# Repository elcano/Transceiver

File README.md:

# Transceiver
Hardware and software to support Transmit/Receive boards

The Elcano Project is an autonomous vehicle control system that runs on a stack of microprocessors, with no operating system and 
no machine learning.
Files that span more than one processor are kept in Elcano/General. The other repositories are:
Elcano/LowLevel – Drive by wire
Elcano/HighLevel – Localization, Route Finding and Pilot
Elcano/Sonar – Detects obstacles from ultrasonic sensors
Elcano/Sweep – Scanse Sweep Lidar for Obstacle Detection
Elcano/QDED – Quadrature Edge Detectors for machine vision
Elcano/Transceiver – Transmit and receive boards for remote control option

The primary autonomous vehicle control comes from HighLevel. Alternatively, the vehicle can be controlled manually, which is the function 
of the Tranceiver board. Depending on what is soldered into the board and which software is used, there are several configurations of the 
transceiver:
 
Transmitter board with joysticks and switches sending via radio.
Receiver board receiving from radio and putting information on CAN bus.
Transmitter via Bluetooth.
Receiver via Bluetooth.
Receiver from a hobbyist RC controller
User interface with joysticks and switches, putting information on CAN bus.

### Required libraries:

#### *Seeed-Studio/CAN-BUS-Shield*
Download as zip from https://github.com/Seeed-Studio/Seeed_Arduino_CAN. 
In Arduino IDE, go to Sketch -> Include Library -> Add .ZIP Library and select the .zip folder.

#### *elcano/Elcano_C2_LowLevel/Can_Protocol.h*
Download “Can_Protocol.h” from https://github.com/elcano/elcano/tree/master/Elcano_C2_LowLevel. 
Create a folder in the location where the Arduino IDE contains it’s libraries on your computer and add this file to the newly created folder.

#### *http://www.airspayce.com/mikem/arduino/RadioHead/classRH__RF69.html*
Download as zip from http://www.airspayce.com/mikem/arduino/RadioHead/index.html. 
In Arduino IDE, go to Sketch -> Include Library -> Add .ZIP Library and select the .zip folder.

#### *elcano/libraries/Settings/SettingsTemplate.h*
Download “SettingsTemplate.h” from https://github.com/elcano/elcano/tree/master/Elcano_C2_LowLevel. 
Create a folder in the location where the Arduino IDE contains it’s libraries on your computer and add this file to the newly created folder.

#### *scanse/sweep-arduino/tree/master/Sweep*
Download as zip from https://github.com/scanse/sweep-arduino. 
Note: need to unzip zip folder and then compress to zip only the sweep folder.
In Arduino IDE, go to Sketch -> Include Library -> Add .ZIP Library and select the .zip folder.

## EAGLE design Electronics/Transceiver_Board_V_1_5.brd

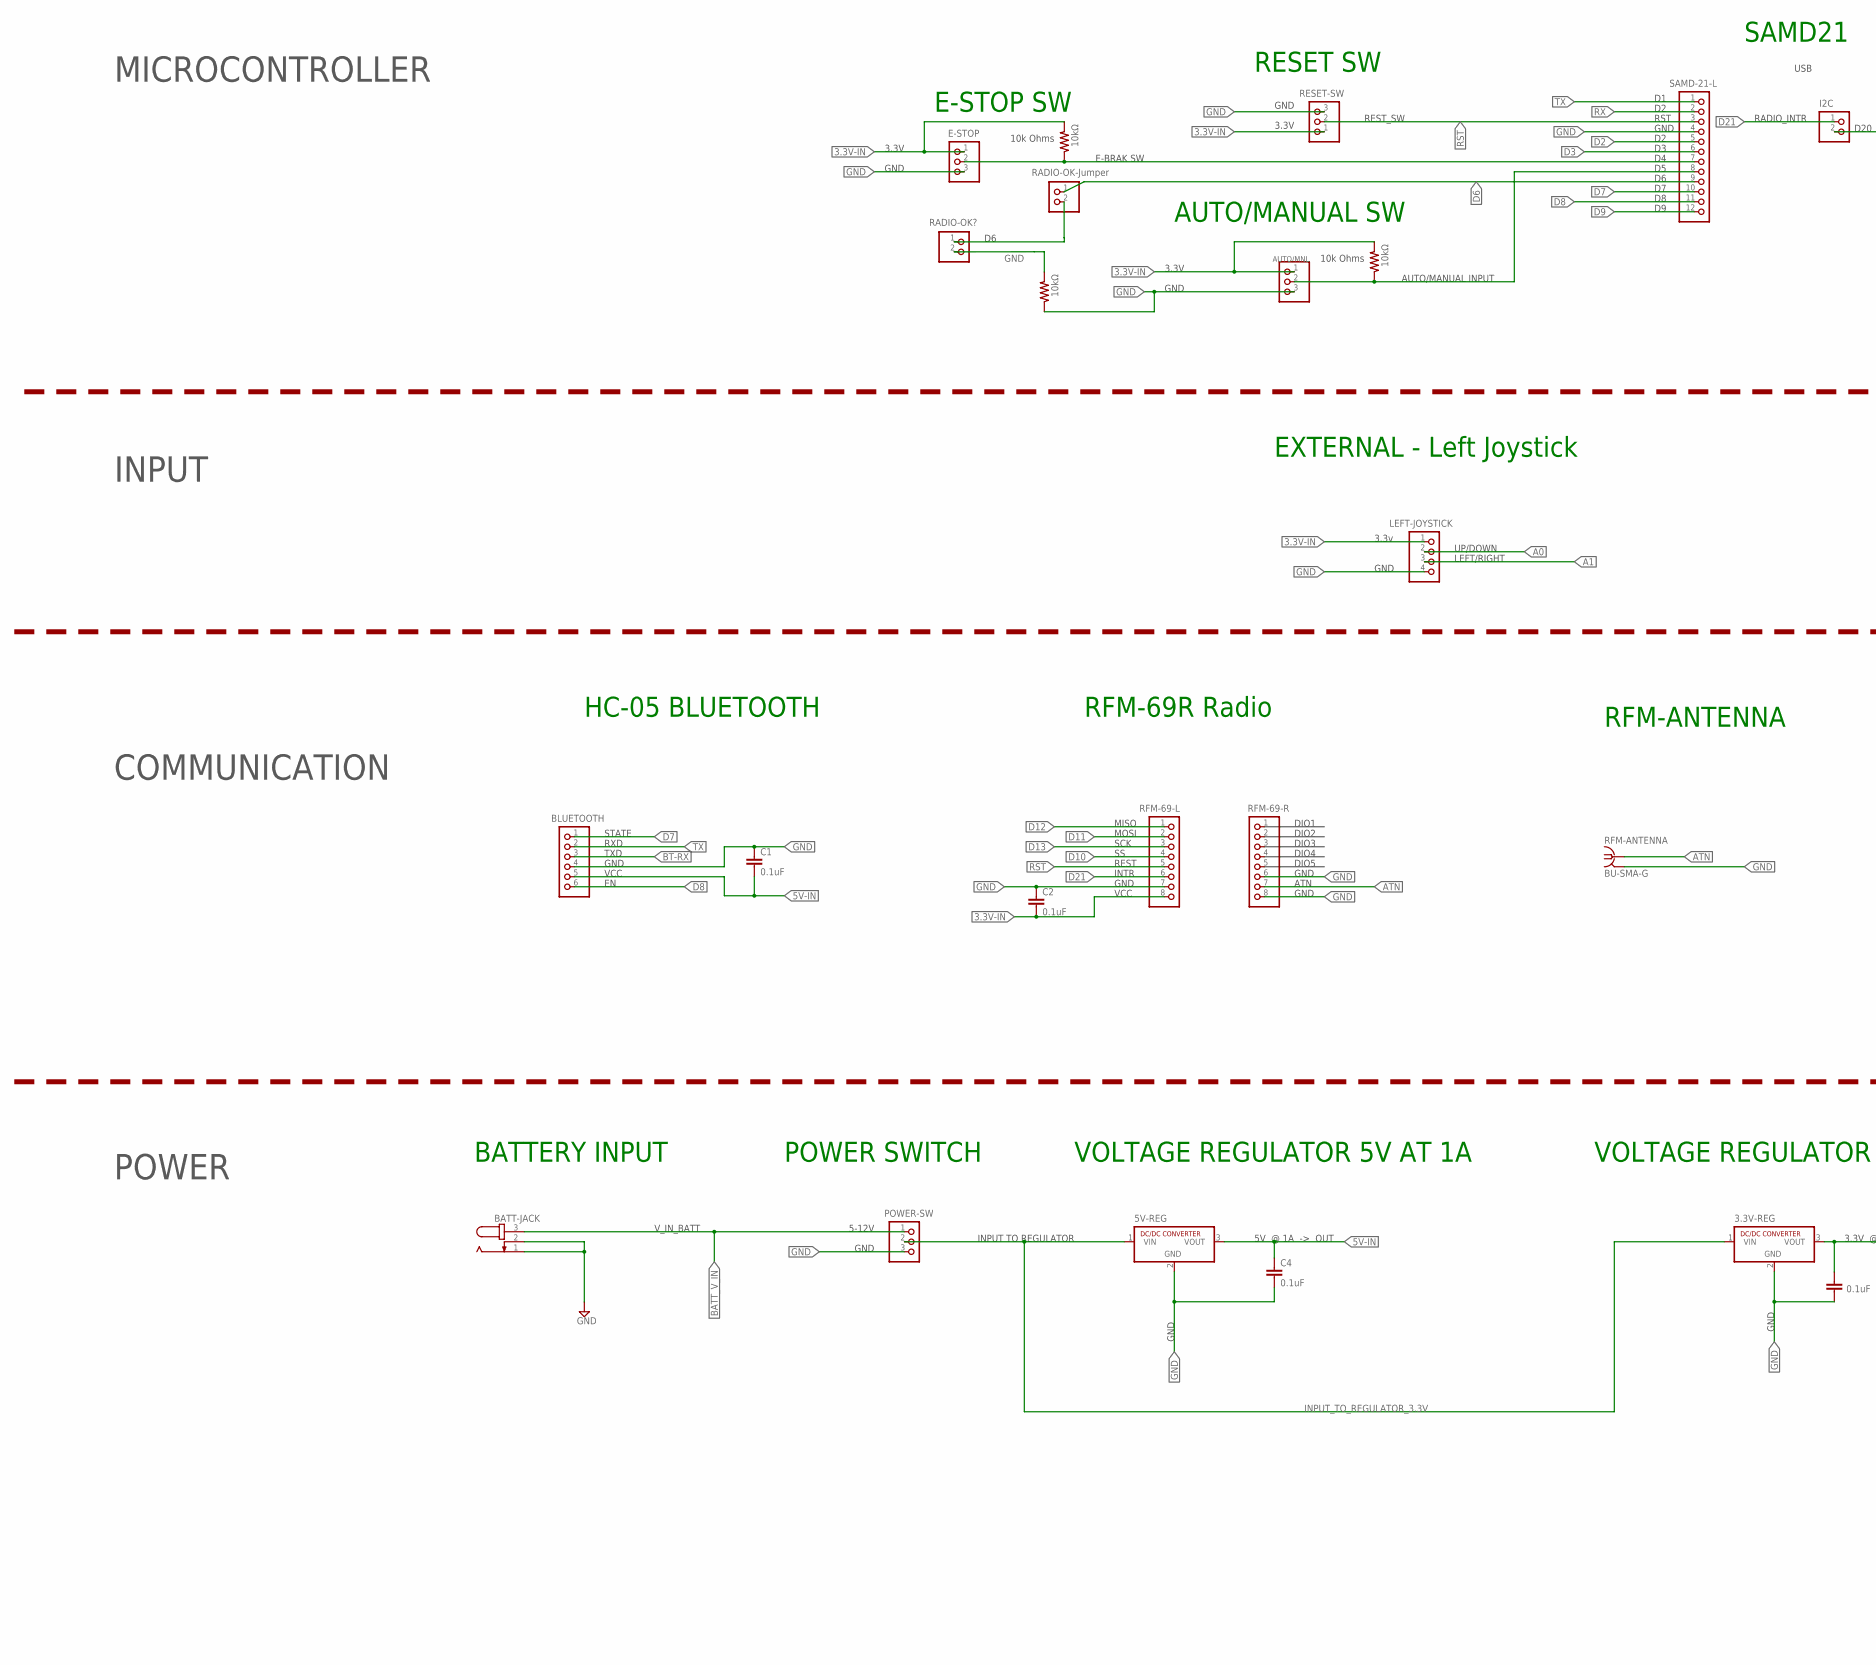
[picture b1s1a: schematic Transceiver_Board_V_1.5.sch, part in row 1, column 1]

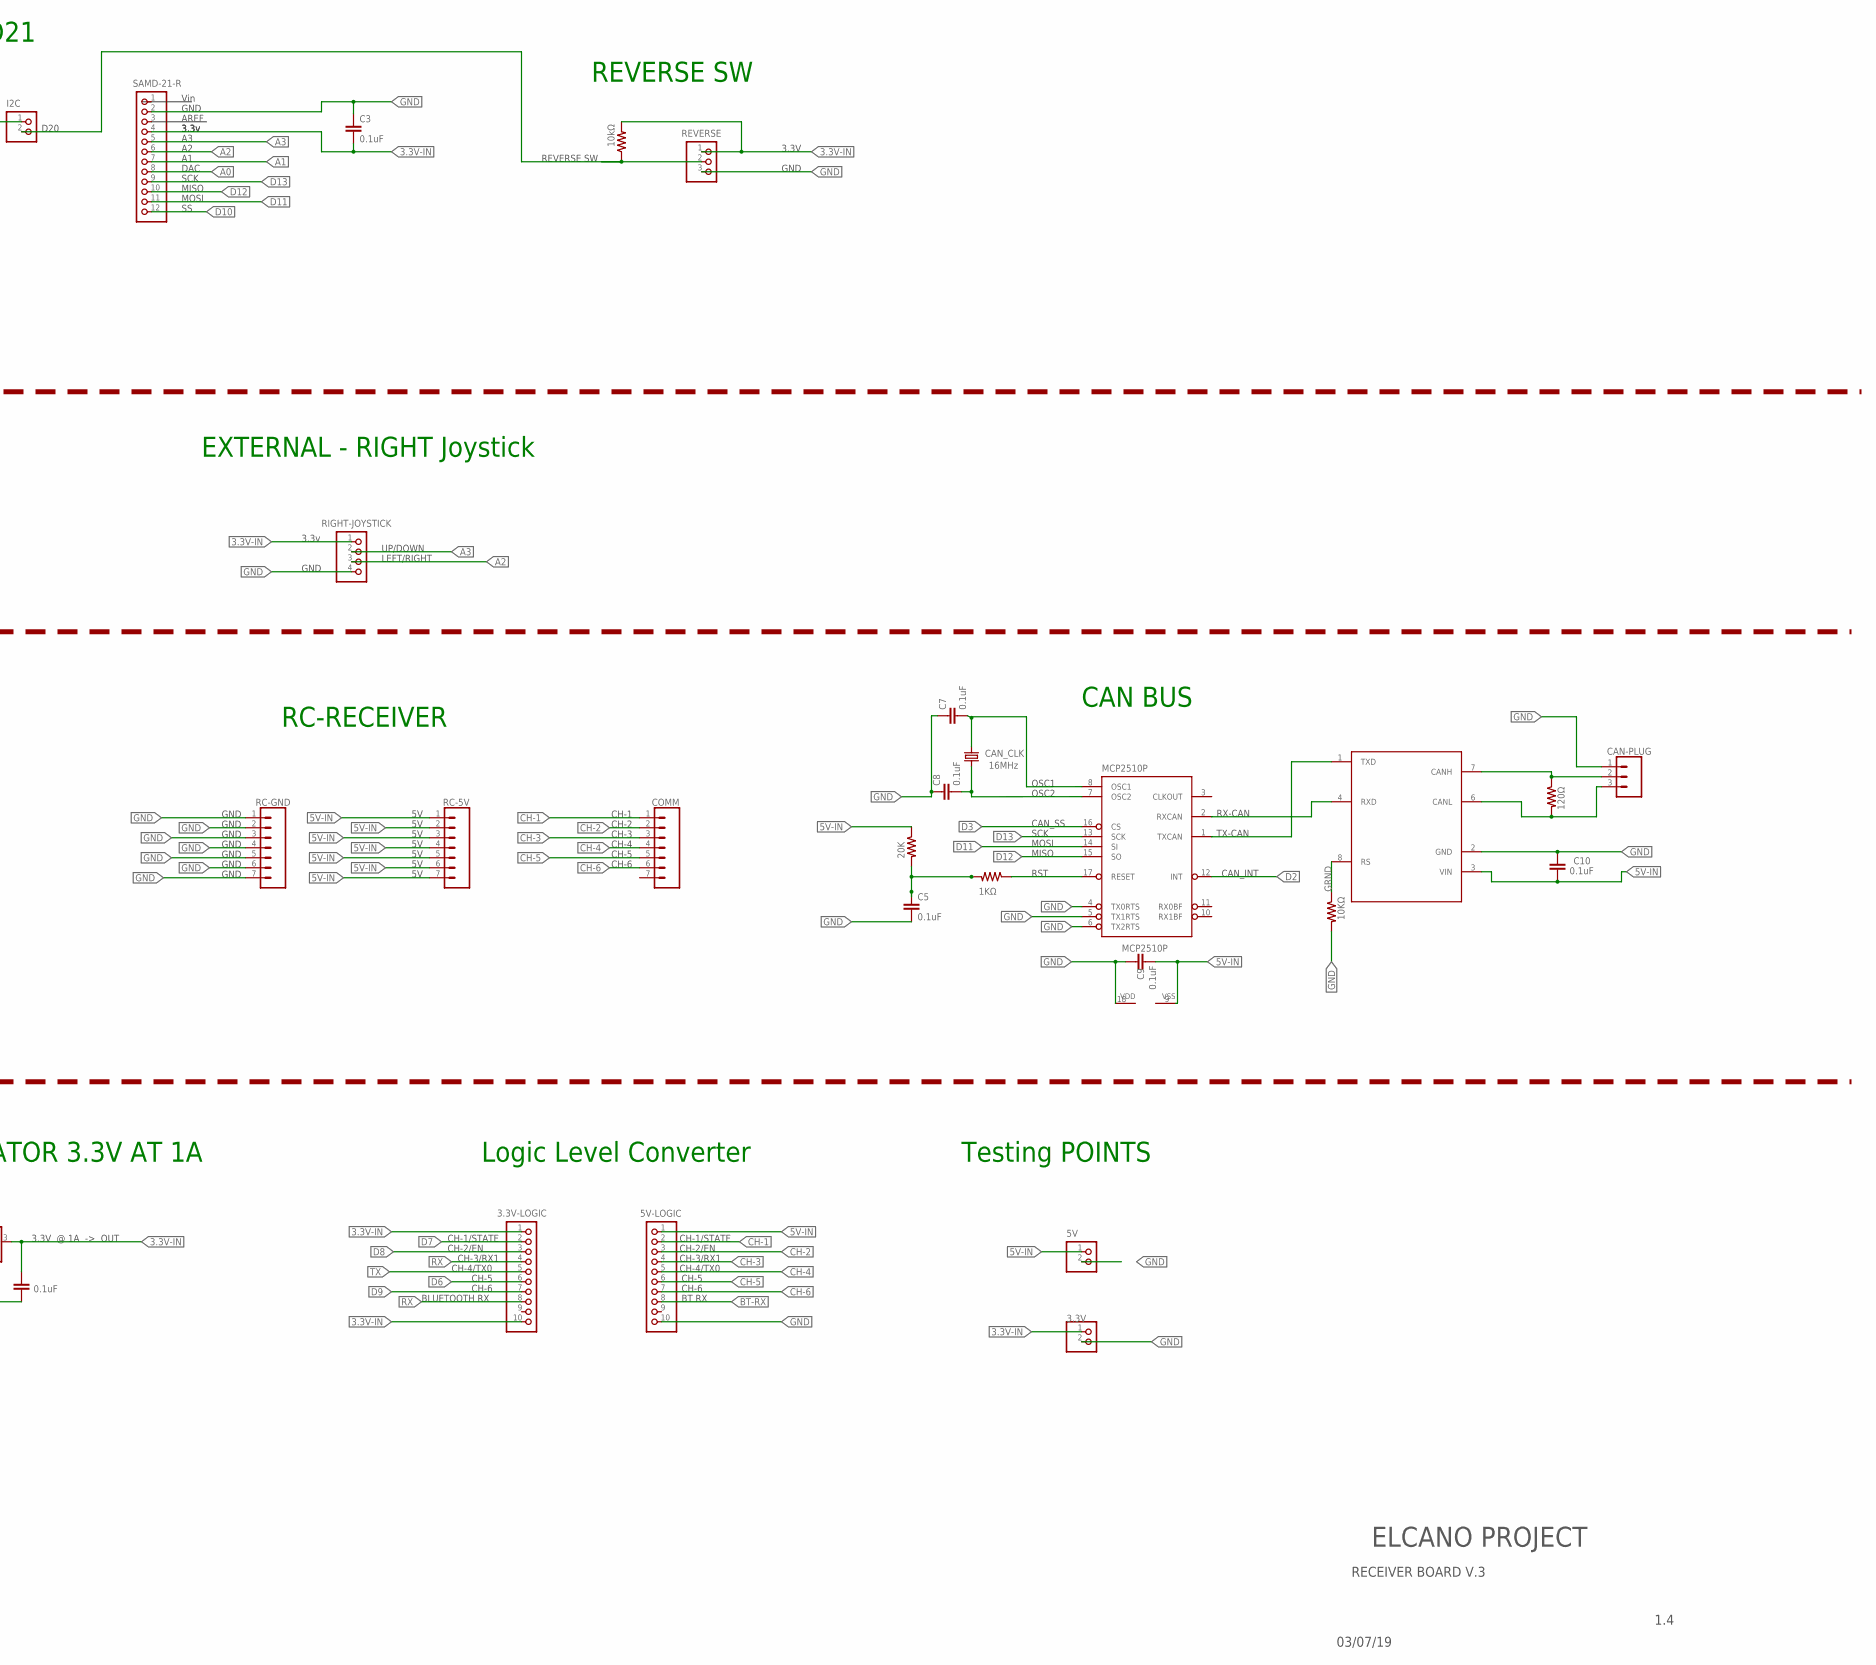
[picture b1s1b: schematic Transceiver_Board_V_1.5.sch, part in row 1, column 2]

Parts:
3.3-LOGIC: 3.3V-LOGIC; 1X10
3.3V-REG: 3.3V REG; SIP3
3.3V-TEST: 3.3V; 1X02
5V-LOGIC: 5V-LOGIC; 1X10
5V-REG: 5V REG; SIP3
5V-TEST: 5V; 1X02
AT/M: AUTO/MNL; 1X03
BATTERY_INPUT_JACK: BATT-JACK; SPC4077
BLUETOOTH: BLUETOOTH; 1X06
C1, C2, C3, C4, C5, C6, C7, C8, C9, C10: 0.1uF; CAP-PTH-SMALL-KIT
CAN_CLK: 16MHz; HC49US
CAN_PLUG: CAN-PLUG; SCREWTERMINAL-5MM-3
COMM: COMM; 1X07
E-STOP: E-STOP; 1X03
I2C: I2C; 1X02
JOY-STICK-L: LEFT-JOYSTICK; 1X04
JOY-STICK-R: RIGHT-JOYSTICK; 1X04
MCP2510P: MCP2510P; DIL18
MCP2551: MCP2551MCP2551; DIL08
POWER-SW: POWER-SW; 1X03
R1, R2, R3, R9: 10kΩ; 0204/7
R5: 1KΩ; 0204/7
R6: 20K; 0204/7
R7: 10KΩ; 0204/7
R8: 120Ω; 0204/7
RADIO-OK1: RADIO-OK-Jumper; 1X02
RADIO-OK?: RADIO-OK?; 1X02
RC-5V: RC-5V; 1X07
RC-GND: RC-GND; 1X07
RESET-SW: RESET-SW; 1X03
REVERSE: REVERSE; 1X03
RFM-69: RFM-69-R; 1X08
RFM-ANTENNA: BU-SMA-G
RFM_L: RFM-69-L; 1X08
SAMD-21_R: SAMD-21-R; 1X12
SAMD_21_L: SAMD-21-L; 1X12

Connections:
3.3V-IN: 3.3-LOGIC.1, 3.3-LOGIC.10, 3.3V-REG.3 (VOUT), 3.3V-TEST.1, AT/M.1, C2.2, C3.2, C6.1, E-STOP.1, JOY-STICK-L.1, JOY-STICK-R.1, R1.2, R2.2, R3.2, RESET-SW.1, REVERSE.1, RFM_L.8, SAMD-21_R.4
3.3V-IN1: C5.1, R5.2, R6.2
5V-IN: 5V-LOGIC.1, 5V-REG.3 (VOUT), 5V-TEST.1, BLUETOOTH.5, C1.2, C4.1, C9.2, C10.2, MCP2510P.9 (VSS), MCP2551.3 (VIN), R6.1, RC-5V.1, RC-5V.2, RC-5V.3, RC-5V.4, RC-5V.5, RC-5V.6, RC-5V.7
A0: JOY-STICK-L.2, SAMD-21_R.8
A1: JOY-STICK-L.3, SAMD-21_R.7
A2: JOY-STICK-R.3, SAMD-21_R.6
A3: JOY-STICK-R.2, SAMD-21_R.5
ATN: RFM-69.7, RFM-ANTENNA.1
BATT_V_IN: BATTERY_INPUT_JACK.3, POWER-SW.1
BT-RX: 5V-LOGIC.8, BLUETOOTH.3
CANH: CAN_PLUG.2, MCP2551.7 (CANH), R8.1
CANL: CAN_PLUG.3, MCP2551.6 (CANL), R8.2
CAN_RST: MCP2510P.17 (RESET), R5.1
CH-1: 5V-LOGIC.2, COMM.1
CH-2: 5V-LOGIC.3, COMM.2
CH-3: 5V-LOGIC.4, COMM.3
CH-4: 5V-LOGIC.5, COMM.4
CH-5: 5V-LOGIC.6, COMM.5
CH-6: 5V-LOGIC.7, COMM.6
D2: MCP2510P.12 (INT), SAMD_21_L.5
D3: MCP2510P.16 (CS), SAMD_21_L.6
D4: E-STOP.2, R1.1, SAMD_21_L.7
D5: AT/M.2, R2.1, SAMD_21_L.8
D6: 3.3-LOGIC.6, RADIO-OK1.1, SAMD_21_L.9
D7: 3.3-LOGIC.2, BLUETOOTH.1, SAMD_21_L.10
D8: 3.3-LOGIC.3, BLUETOOTH.6, SAMD_21_L.11
D9: 3.3-LOGIC.7, SAMD_21_L.12
D10: RFM_L.4, SAMD-21_R.12
D11: MCP2510P.14 (SI), RFM_L.2, SAMD-21_R.11
D12: MCP2510P.15 (SO), RFM_L.1, SAMD-21_R.10
D13: MCP2510P.13 (SCK), RFM_L.3, SAMD-21_R.9
D20: I2C.2, R3.1, REVERSE.2
D21: I2C.1, RFM_L.6
GND: 3.3V-REG.2 (GND), 3.3V-TEST.2, 5V-LOGIC.10, 5V-REG.2 (GND), 5V-TEST.2, AT/M.3, BATTERY_INPUT_JACK.1, BATTERY_INPUT_JACK.2, BLUETOOTH.4, C1.1, C2.1, C3.1, C4.2, C5.2, C6.2, C7.1, C8.1, C9.1, C10.1, CAN_PLUG.1, E-STOP.3, JOY-STICK-L.4, JOY-STICK-R.4, MCP2510P.4 (TX0RTS), MCP2510P.5 (TX1RTS), MCP2510P.6 (TX2RTS), MCP2510P.18 (VDD), MCP2551.2 (GND), POWER-SW.3, R7.2, R9.1, R9.2, RADIO-OK?.2, RC-GND.1, RC-GND.2, RC-GND.3, RC-GND.4, RC-GND.5, RC-GND.6, RC-GND.7, RESET-SW.3, REVERSE.3, RFM-69.6, RFM-69.8, RFM-ANTENNA.2, RFM-ANTENNA.3 (2), RFM-ANTENNA.4 (2), RFM-ANTENNA.5 (2), RFM_L.7, SAMD-21_R.2, SAMD_21_L.4
GRND: MCP2551.8 (RS), R7.1
INPUT_TO_REGULATOR_3.3V: 3.3V-REG.1 (VIN), 5V-REG.1 (VIN), POWER-SW.2
unnamed: RADIO-OK1.2, RADIO-OK?.1
OSC1: C7.2, CAN_CLK.1, MCP2510P.8 (OSC1)
OSC2: C8.2, CAN_CLK.2, MCP2510P.7 (OSC2)
RST: RESET-SW.2, RFM_L.5, SAMD_21_L.3
RX: 3.3-LOGIC.4, 3.3-LOGIC.8, SAMD_21_L.2
RX-CAN: MCP2510P.2 (RXCAN), MCP2551.4 (RXD)
TX: 3.3-LOGIC.5, BLUETOOTH.2, SAMD_21_L.1
TX-CAN: MCP2510P.1 (TXCAN), MCP2551.1 (TXD)

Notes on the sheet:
RST
GND
Vin
3.3v
DAC
SCK
MISO
MOSI
SAMD21
RFM-69R Radio
USB
RFM-ANTENNA
EXTERNAL - Left Joystick
DIO1
DIO2
DIO3
DIO4
DIO5
ATN
UP/DOWN
LEFT/RIGHT
EXTERNAL - RIGHT Joystick
STATE
RXD
TXD
VCC
HC-05 BLUETOOTH
E-BRAK SW
3.3V
AUTO/MANUAL INPUT
REVERSE SW
E-STOP SW
AUTO/MANUAL SW
REST_SW
RESET SW
VOLTAGE REGULATOR 5V AT 1A
BATTERY INPUT
VOLTAGE REGULATOR 3.3V AT 1A
REST
Testing POINTS

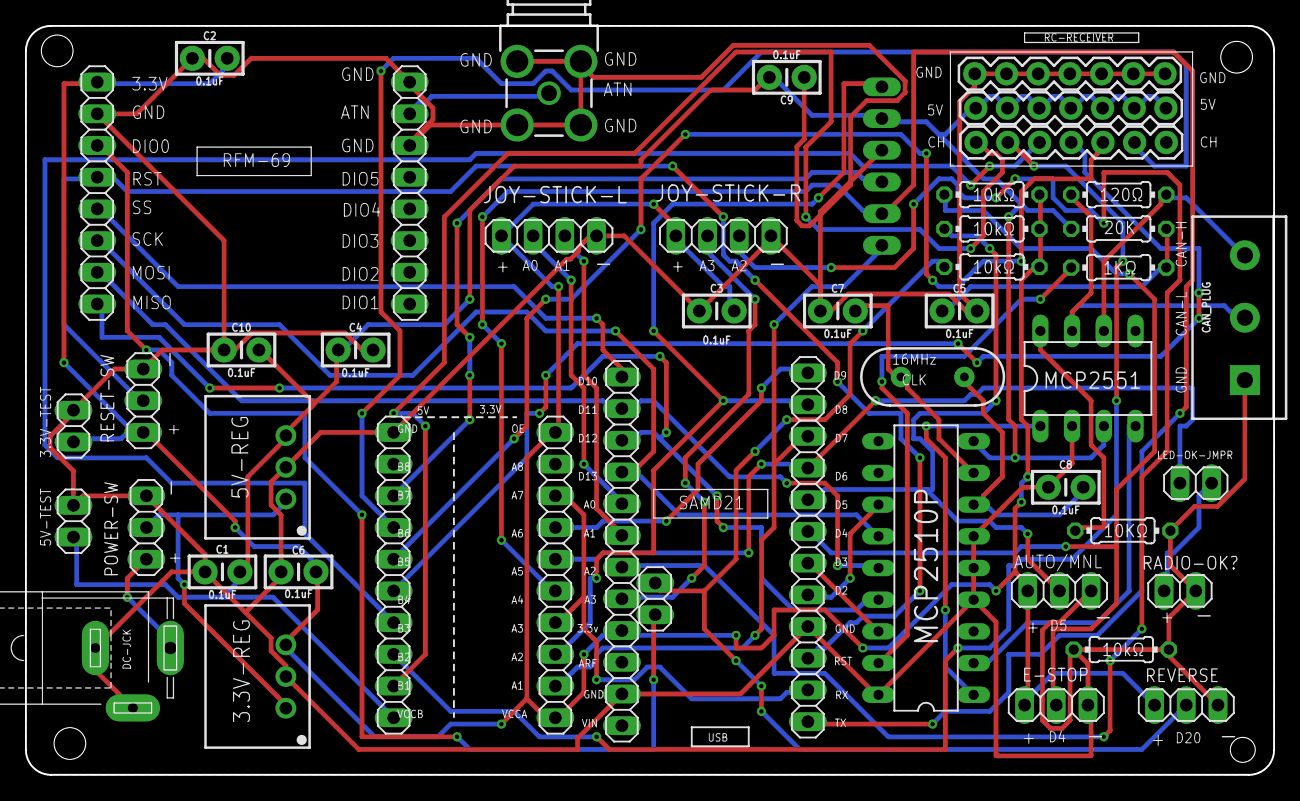
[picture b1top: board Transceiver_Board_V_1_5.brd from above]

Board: 2 copper layers, 100.0 x 60.0 mm, 48 parts (1 on the bottom side), 44 nets.

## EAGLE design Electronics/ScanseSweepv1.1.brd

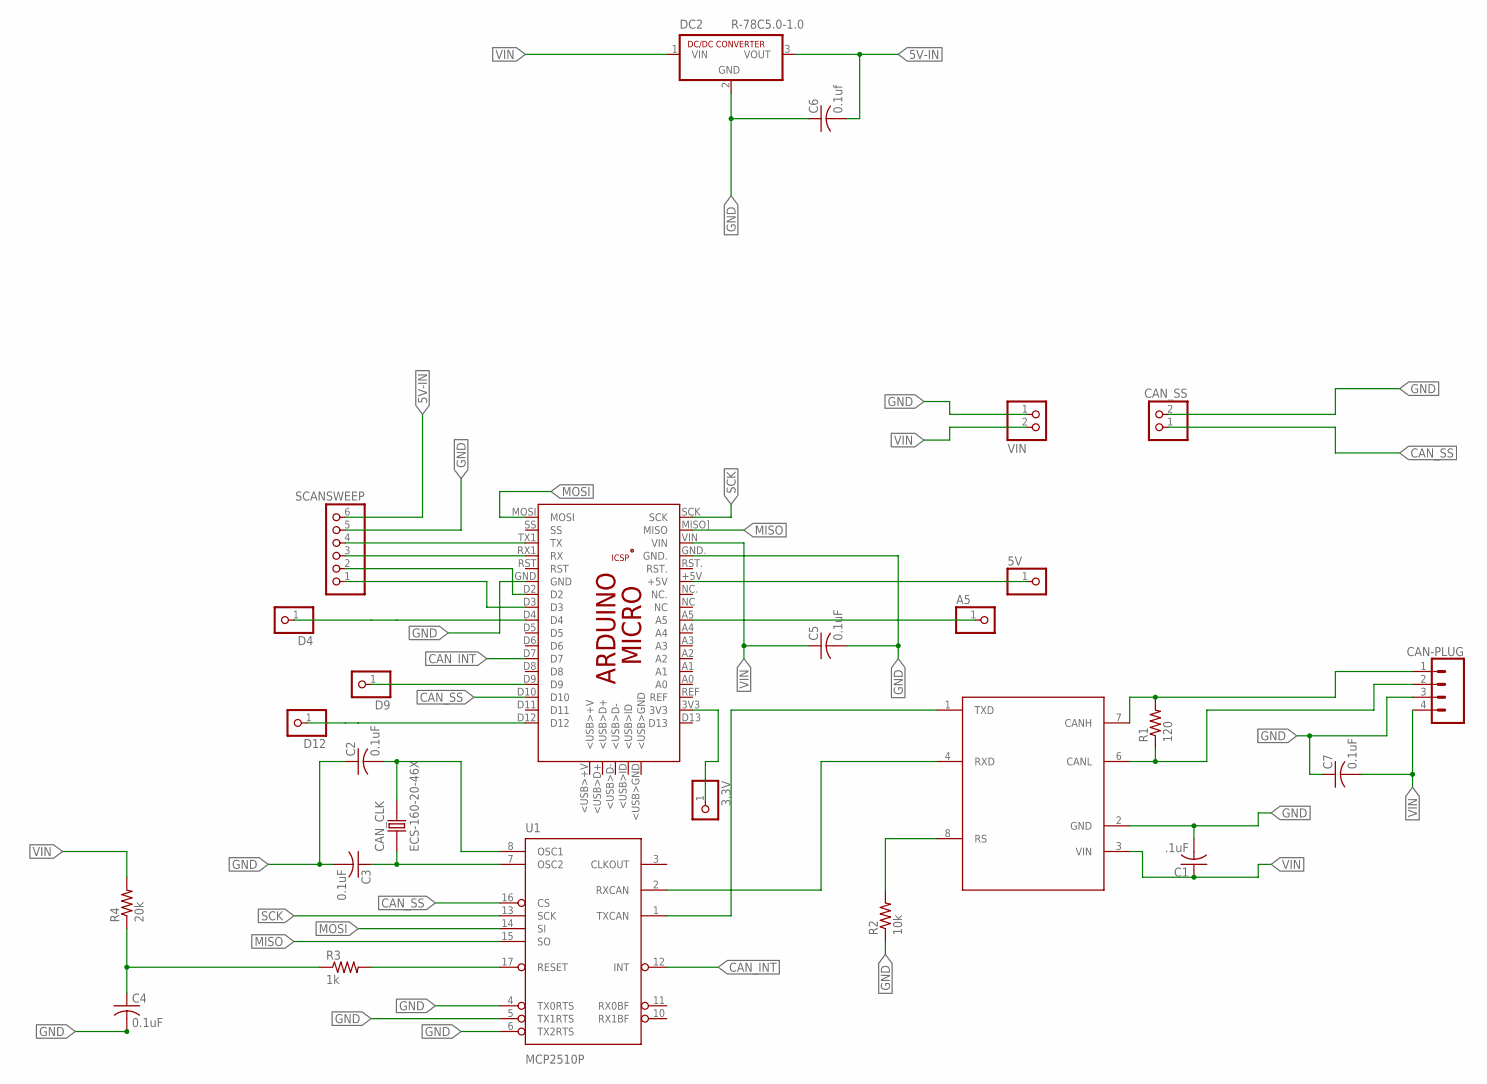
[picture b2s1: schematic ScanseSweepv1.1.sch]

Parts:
3.3V, 5V: PINHD-1X1; 1X01
A5: PINHD-1X1; 1X01
C1: .1uF; C025-024X044
C2, C3, C4, C5, C7: 0.1uF; C025-024X044
C6: 0.1uf; C025-024X044
CAN_CLK: ECS-160-20-46X; XTAL_ECS-160-20-46X
CAN_SS_TEST: CAN_SS; 1X02
D4, D9, D12: PINHD-1X1; 1X01
DC2: R-78C5.0-1.0; SIP3
J1: CAN-PLUG; SCREWTERMINAL-3.5MM-4
PCB1: ARDUINO_MICRO
R1: 120; 0204/5
R2: 10k; 0204/5
R3: 1k; 0204/5
R4: 20k; 0204/5
SCANSESWEEP: SCANSWEEP; 1X06
U1: MCP2510P; DIL18
U$1: MCP2551MCP2551; DIL08
VIN_TEST: VIN; 1X02

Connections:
3.3V: 3.3V.1, PCB1.3V3
5V: 5V.1, PCB1.+5V
5V-IN: C6.2, DC2.3 (VOUT), SCANSESWEEP.6
A5: A5.1, PCB1.A5
CANH: J1.1, R1.2, U$1.7 (CANH)
CANL: J1.2, R1.1, U$1.6 (CANL)
CAN_INT: PCB1.D7, U1.12 (INT)
CAN_SS: CAN_SS_TEST.1, PCB1.D10, U1.16 (CS)
D2: PCB1.D2, SCANSESWEEP.2
D3: PCB1.D3, SCANSESWEEP.1
D4: D4.1, PCB1.D4
D9: D9.1, PCB1.D9
D12: D12.1, PCB1.D12
GND: C1.2, C2.1, C3.2, C4.2, C5.2, C6.1, C7.1, CAN_SS_TEST.2, DC2.2 (GND), J1.3, PCB1.GND, PCB1.GND., R2.1, SCANSESWEEP.5, U1.4 (TX0RTS), U1.5 (TX1RTS), U1.6 (TX2RTS), U$1.2 (GND), VIN_TEST.1
MISO: PCB1.MISO] (MISO), U1.15 (SO)
MOSI: PCB1.MOSI, U1.14 (SI)
unnamed: C4.1, R3.1, R4.1
OSC1: C2.2, CAN_CLK.2, U1.8 (OSC1)
OSC2: C3.1, CAN_CLK.1, U1.7 (OSC2)
RESET: R3.2, U1.17 (RESET)
RS: R2.2, U$1.8 (RS)
RX: PCB1.RX1 (RX), SCANSESWEEP.3
RXCAN: U1.2 (RXCAN), U$1.4 (RXD)
SCK: PCB1.SCK, U1.13 (SCK)
TX: PCB1.TX1 (TX), SCANSESWEEP.4
TXCAN: U1.1 (TXCAN), U$1.1 (TXD)
VIN: C1.1, C5.1, C7.2, DC2.1 (VIN), J1.4, PCB1.VIN, R4.2, U$1.3 (VIN), VIN_TEST.2

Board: 2 copper layers, 26 parts (0 on the bottom side), 27 nets, no tracks yet.

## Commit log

2015-03-13 added arduino files
2015-03-13 added report
2019-06-10 Archive all old RC Code from previous student
2019-06-10 Add Bluetooth and RC code. Bluetooth is completed with CAN BUS (CAN BUS - Not tested yet). RC is being developed.
2019-08-24 End of Summer 2019 commit (Maneuverability Team documents and working code
2019-08-27 Added electronics files for transceiver & sweep
2019-12-13 Fall2019 Transciever update
2019-12-13 Fall2019 Transceiver Update and Changes.txt
2023-03-04 pushing all changes made to files - need to change CAN library
2023-03-04 edit README.md
2023-03-04 edit README.md pt2
2023-03-04 edit README.md pt3
2023-03-04 edit README.md pt4
2023-03-04 edit README.md pt5
2023-03-04 updated CAN-BUS-Shield library and files to compile
2023-03-07 add documentation and format for pull request

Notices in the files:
parts and their libraries:
SparkFun-Connectors: Licensing: Creative Commons ShareAlike 4.0 International - https://creativecommons.org/licenses/by-sa/4.0
